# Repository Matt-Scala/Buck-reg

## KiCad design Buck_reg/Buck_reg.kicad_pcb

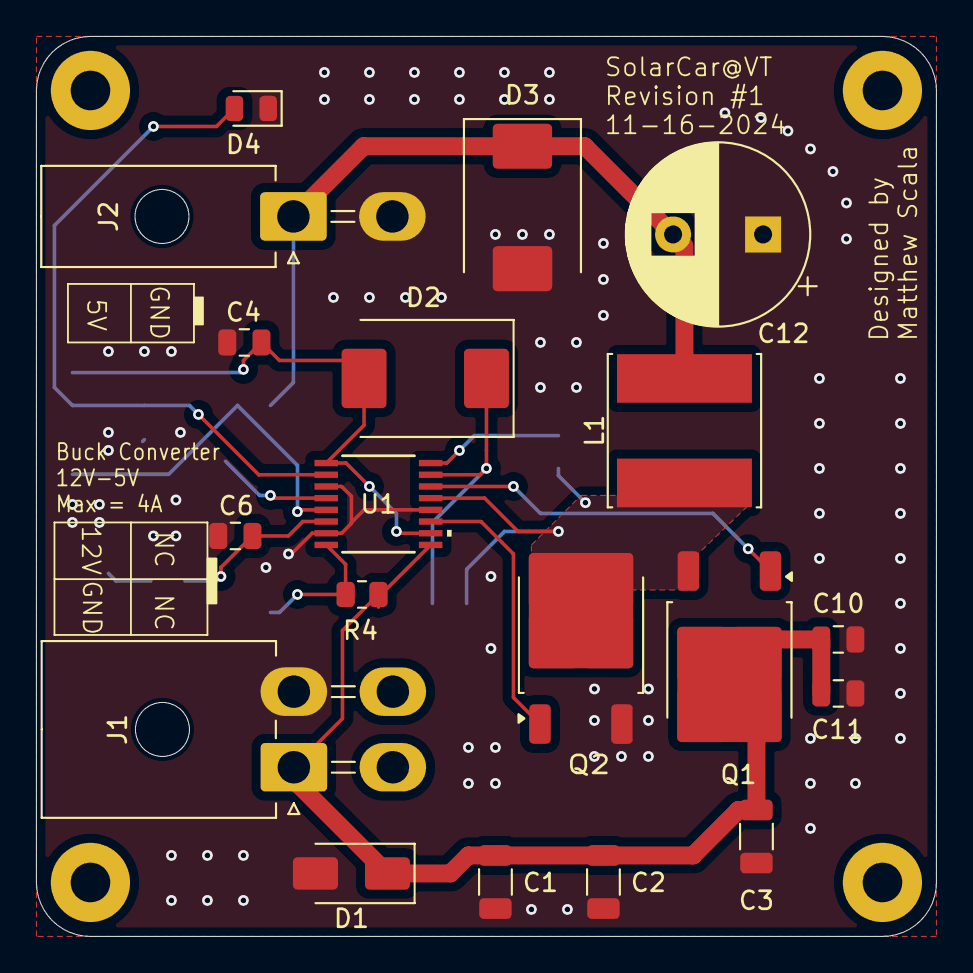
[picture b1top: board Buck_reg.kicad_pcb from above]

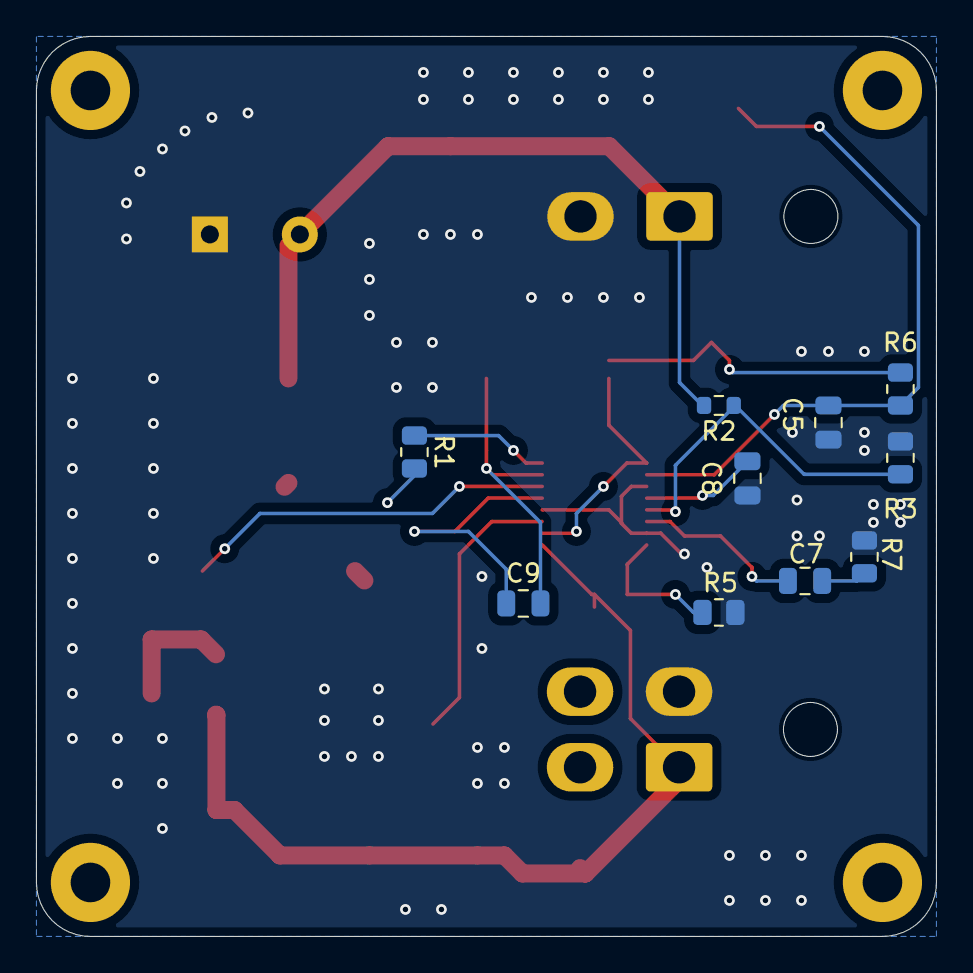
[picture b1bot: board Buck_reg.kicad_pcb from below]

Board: 2 copper layers, 50.0 x 50.0 mm, 33 parts (10 on the bottom side), 15 nets.

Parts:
C1: 22-100 uF 6-10 of them; C_1206_3216Metric
C2, C3: C_1206_3216Metric
C4, C8, C9: .1 uF; C_0805_2012Metric
C5, C10, C11: 10 uF; C_0805_2012Metric
C6: 50 pF; C_0805_2012Metric
C7: .15 uF; C_0805_2012Metric
C12: CP_Radial_D10.0mm_P5.00mm
D1: PTVS12VZ1USK; D_SMA
D2: D_Schottky; D_SMC
D3: PTVS5V0Z1USK; D_SMC
D4: LED; LED_0805_2012Metric
H1, H2, H3, H4: MountingHole; MountingHole_2.2mm_M2_Pad
J1: Conn_01x04_Pin; Molex_Mini-Fit_Jr_5569-04A2_2x02_P4.20mm_Horizontal
J2: Conn_01x02_Pin; Molex_Mini-Fit_Jr_5569-02A2_2x01_P4.20mm_Horizontal
L1: 22 uH(any low value above 4uH); L_Cenker_CKCS8080
Q1, Q2: NMOS; TO-252-2 (corrected pin order)
R1: 32; R_0805_2012Metric
R2: 16.4k; R_0603_1608Metric
R3, R4: 2.67k; R_0805_2012Metric
R5: 24k; R_0805_2012Metric
R6: 10k; R_0805_2012Metric
R7: 3.16k; R_0805_2012Metric
U1: MIC2130-4YTSE-TR; TSSOP-16_K4-16-1_MCH

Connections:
/L_Junction: C9.1, L1.1, Q1.3 (S), Q2.1 (D), R1.2, U1.13 (SW)
GND: C1.1, C2.2, C3.2, C4.1, C5.1, C6.1, C8.1, C10.2, C11.1, C12.1, D1.2 (A), D3.2 (A), D4.1 (K), J1.2, J2.2, Q2.3 (S), R3.1, R5.2, R7.1, U1.3 (HCL/AGND2), U1.7 (AGND1), U1.12 (PGND)
unnamed: C7.1, R7.2
unnamed: C4.2, D2.2 (A), R6.2, U1.1 (AVDD), U1.10 (VDD)
unnamed: C9.2, D2.1 (K), U1.15 (BST)
unnamed: C12.2, D3.1 (K), J2.1, L1.2, R2.2
unnamed: C5.2, D4.2 (A), R6.1, U1.2 (PGOOD)
unnamed: Q1.2 (G), U1.14 (HSD)
unnamed: Q2.2 (G), U1.11 (LSD)
unnamed: C6.2, C7.2, U1.6 (COMP)
unnamed: R1.1, U1.16 (CS)
unnamed: R4.2, R5.1, U1.8 (EN/UVLO)
unnamed: R2.1, R3.2, U1.5 (FB)
unnamed: C8.2, U1.4 (SS)
VCC: C1.2, C2.1, C3.1, C10.1, C11.2, D1.1 (K), J1.1, Q1.1 (D), R4.1, U1.9 (VIN)
